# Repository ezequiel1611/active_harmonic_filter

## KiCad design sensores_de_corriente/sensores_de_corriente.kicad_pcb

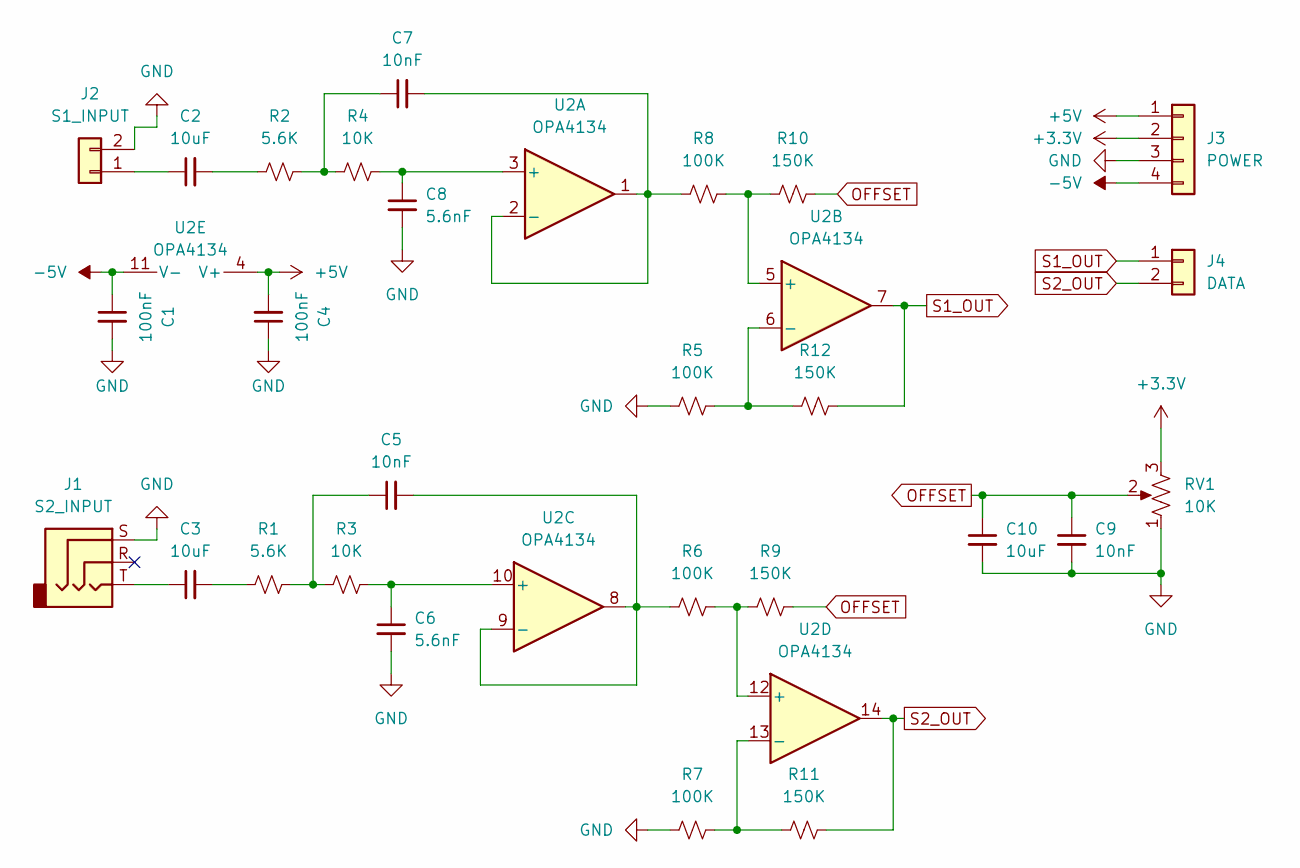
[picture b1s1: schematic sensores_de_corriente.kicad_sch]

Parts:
C1, C4: 100nF; C_Disc_D5.0mm_W2.5mm_P5.00mm
C2, C3, C10: 10uF; CP_Radial_D5.0mm_P2.50mm
C5, C7: 10nF; C_Disc_D10.5mm_W5.0mm_P10.00mm
C6, C8: 5.6nF; C_Disc_D5.0mm_W2.5mm_P5.00mm
C9: 10nF; C_Disc_D7.5mm_W5.0mm_P7.50mm
J1: S2_INPUT; Jack_3.5mm_CUI_SJ1-3525N_Horizontal
J2: S1_INPUT; TerminalBlock_bornier-2_P5.08mm
J3: POWER; PinSocket_1x04_P2.54mm_Vertical
J4: DATA; PinSocket_1x02_P2.54mm_Vertical
R1, R2: 5.6K; R_Axial_DIN0207_L6.3mm_D2.5mm_P10.16mm_Horizontal
R3, R4: 10K; R_Axial_DIN0207_L6.3mm_D2.5mm_P10.16mm_Horizontal
R5, R6, R7, R8: 100K; R_Axial_DIN0207_L6.3mm_D2.5mm_P10.16mm_Horizontal
R9, R10, R11, R12: 150K; R_Axial_DIN0207_L6.3mm_D2.5mm_P10.16mm_Horizontal
RV1: 10K; Potentiometer_Bourns_3005_Horizontal
U2: OPA4134; SOIC-14_3.9x8.7mm_P1.27mm

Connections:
+3.3V: J3.2, RV1.3
+5V: C4.2, J3.1, U2.4 (V+)
-5V: C1.1, J3.4, U2.11 (V-)
GND: C1.2, C4.1, C6.2, C8.2, C9.2, C10.2, J1.S, J2.2, J3.3, R5.1, R7.1, RV1.1
unnamed: C2.2, R2.1
unnamed: C3.1, J1.T
unnamed: C3.2, R1.1
unnamed: C5.1, R1.2, R3.1
unnamed: C7.1, R2.2, R4.1
unnamed: C2.1, J2.1
unnamed: C8.1, R4.2, U2.3 (+)
unnamed: C7.2, R8.1, U2.1, U2.2 (-)
unnamed: R8.2, R10.1, U2.5 (+)
unnamed: R5.2, R12.1, U2.6 (-)
unnamed: C6.1, R3.2, U2.10 (+)
unnamed: C5.2, R6.1, U2.8, U2.9 (-)
unnamed: R6.2, R9.1, U2.12 (+)
unnamed: R7.2, R11.1, U2.13 (-)
OFFSET: C9.1, C10.1, R9.2, R10.2, RV1.2
S1_OUT: J4.1, R12.2, U2.7
S2_OUT: J4.2, R11.2, U2.14

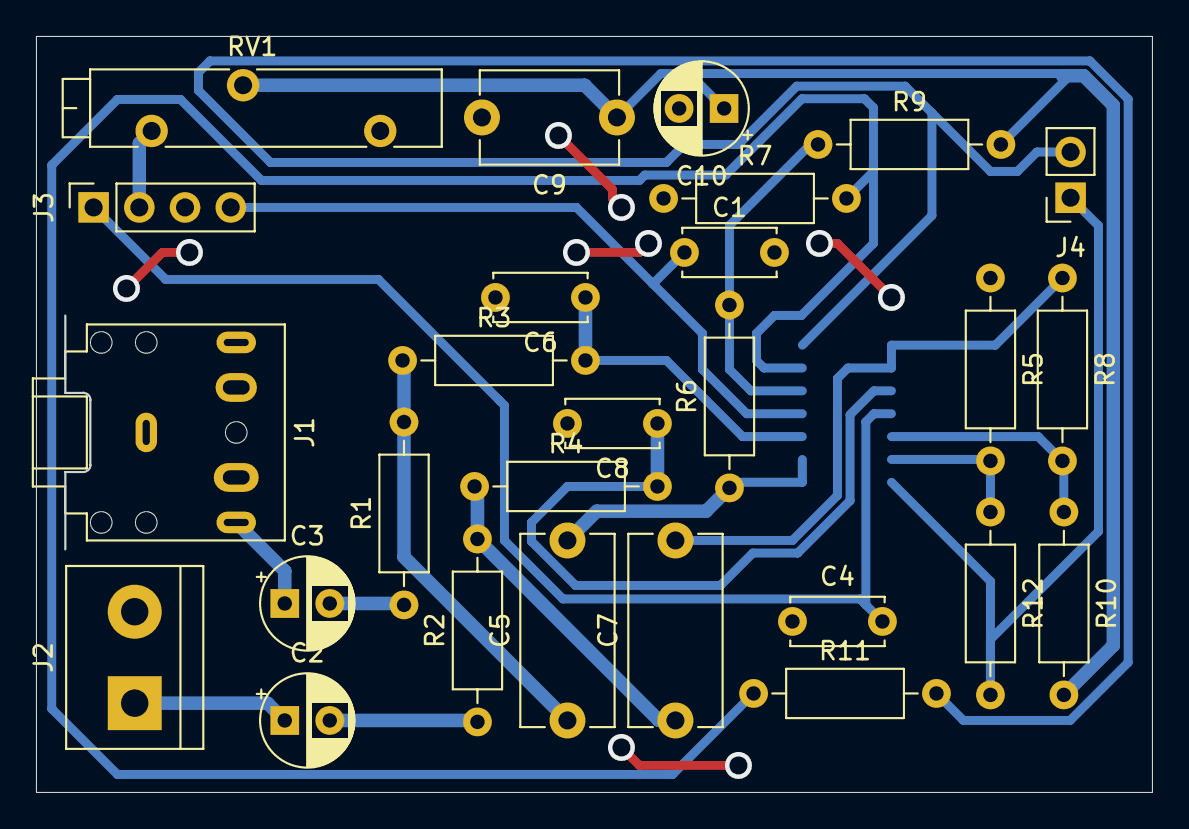
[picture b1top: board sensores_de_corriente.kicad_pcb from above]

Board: 2 copper layers, 61.9 x 41.9 mm, 28 parts (1 on the bottom side), 21 nets.

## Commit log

2024-08-05 Circuitos Simulados en Proteus
    Simulación de los circuitos del sensor de voltaje y de los sensores de corriente en Proteus.
2024-08-05 Diseño Placa de Sensores y Raspberry Pi Pico
    Circuito esquemático y PCB de los circuitos de adecuación de señales para medir tensión y corriente con el microcontrolador RP2040
2024-08-05 Footprints, Symbols and 3D Models
    Símbolos, huellas y modelos 3D (STEP) de componentes para la placa de adecuación de señales.
2024-08-22 Placa de prueba para los sensores de corriente
    Esta placa con el OPA4134 permite hace pruebas en simultáneo de los dos sensores de corriente SCT013.
